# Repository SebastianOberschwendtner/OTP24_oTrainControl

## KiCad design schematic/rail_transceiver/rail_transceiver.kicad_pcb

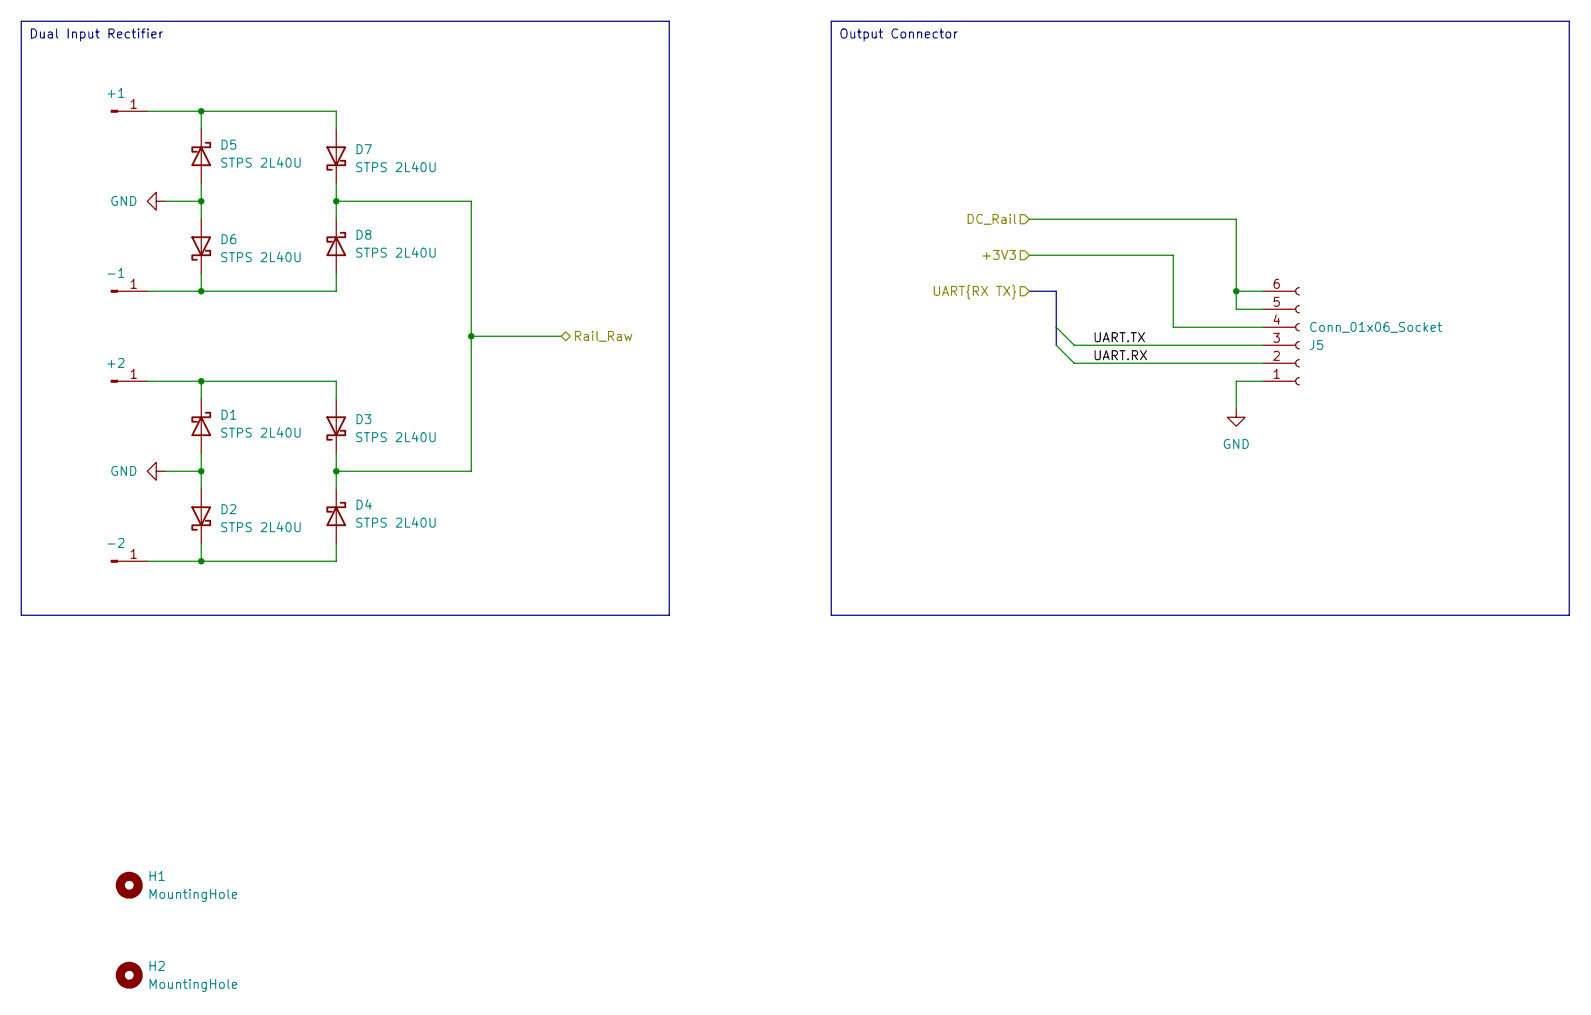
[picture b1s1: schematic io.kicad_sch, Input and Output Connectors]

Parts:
+1, +2: Conn_01x01_Pin; SolderWirePad_1x01_SMD_1x2mm
-1, -2: Conn_01x01_Pin; SolderWirePad_1x01_SMD_1x2mm
D1, D2, D3, D4, D5, D6, D7, D8: STPS 2L40U; D_SMB
H1, H2: MountingHole; MountingHole_2.2mm_M2
J5: Conn_01x06_Socket; Molex_SPOX_5268-06A_1x06_P2.50mm_Horizontal

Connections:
+3V3: J5.4; also elsewhere on the board
/Connectors/DC_Rail: J5.5, J5.6; also elsewhere on the board
/Connectors/Rail_Raw: D3.1 (K), D4.1 (K), D7.1 (K), D8.1 (K); also elsewhere on the board
/Connectors/UART.RX: J5.2; also elsewhere on the board
/Connectors/UART.TX: J5.3; also elsewhere on the board
GND: D1.2 (A), D2.2 (A), D5.2 (A), D6.2 (A), J5.1; also elsewhere on the board
unnamed: +1.1, D5.1 (K), D7.2 (A)
unnamed: +2.1, D1.1 (K), D3.2 (A)
unnamed: -1.1, D6.1 (K), D8.2 (A)
unnamed: -2.1, D2.1 (K), D4.2 (A)

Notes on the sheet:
Output Connector
Dual Input Rectifier

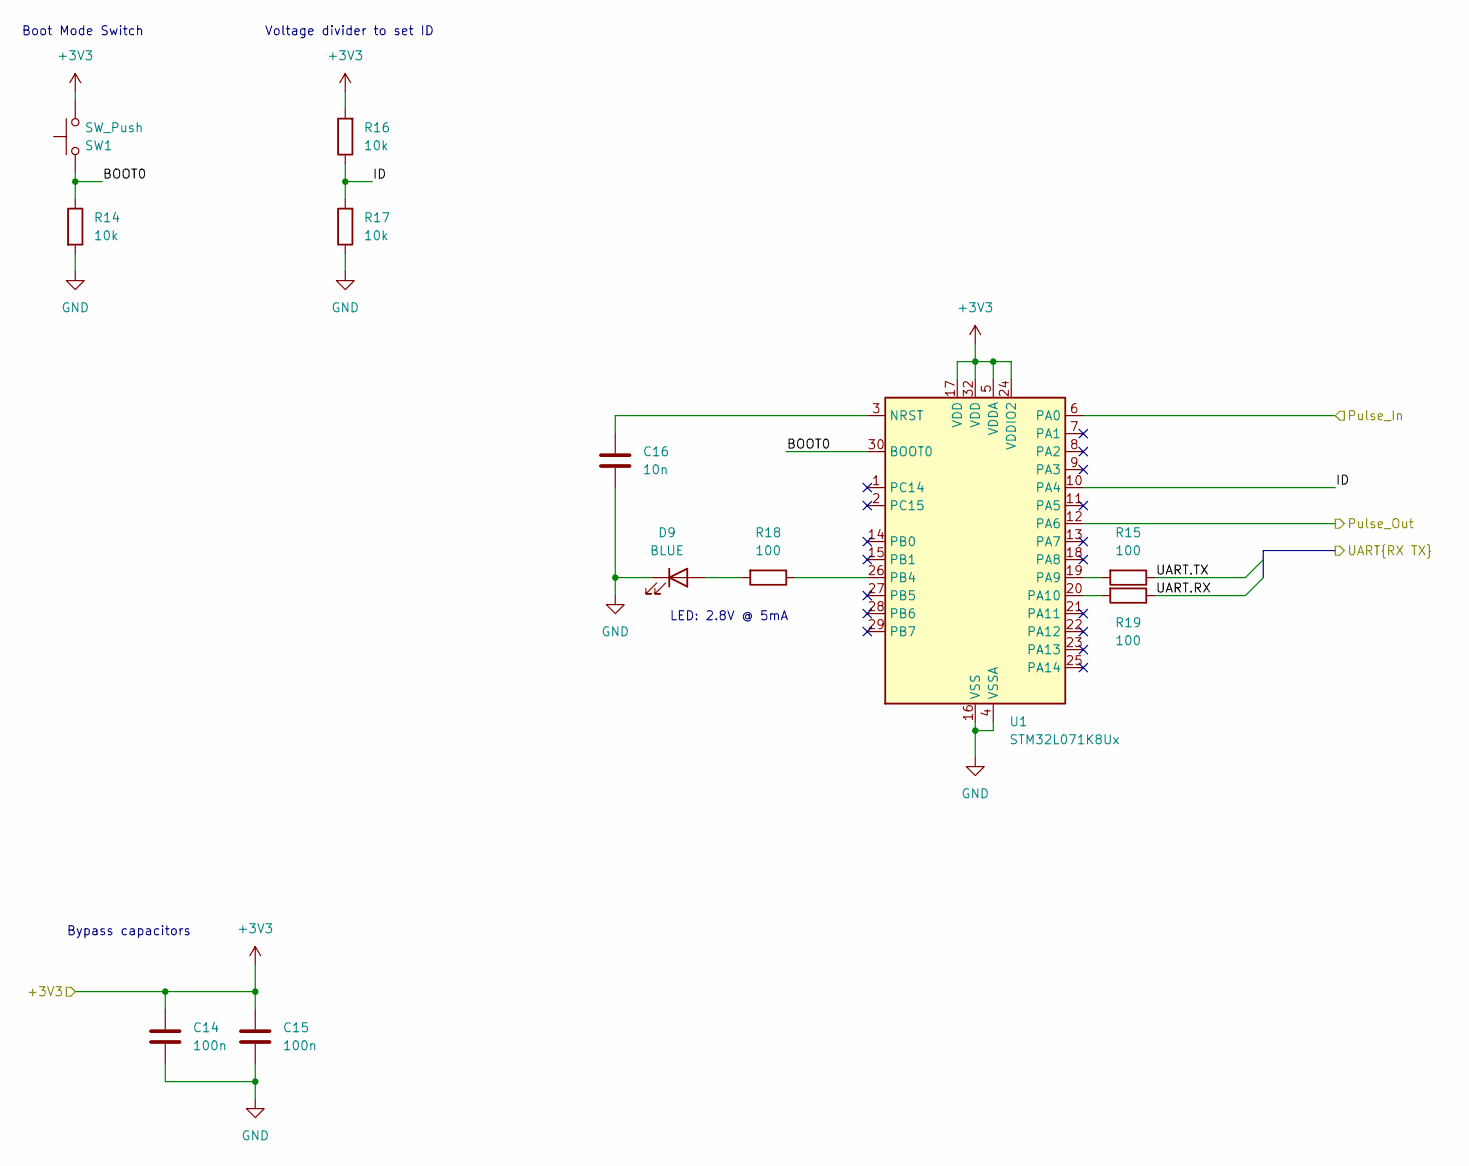
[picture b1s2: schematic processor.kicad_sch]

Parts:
C14, C15: 100n; C_0805_2012Metric_Pad1.18x1.45mm_HandSolder
C16: 10n; C_0805_2012Metric_Pad1.18x1.45mm_HandSolder
D9: BLUE; LED_0603_1608Metric_Pad1.05x0.95mm_HandSolder
R14, R16, R17: 10k; R_0805_2012Metric_Pad1.20x1.40mm_HandSolder
R15, R18, R19: 100; R_0805_2012Metric_Pad1.20x1.40mm_HandSolder
SW1: SW_Push; SW_SPST_Wuerth_WS-TASU_SMT
U1: STM32L071K8Ux; QFN-32-1EP_5x5mm_P0.5mm_EP3.45x3.45mm

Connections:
+3V3: C14.1, C15.1, R16.2, SW1.1, U1.5 (VDDA), U1.17 (VDD), U1.24 (VDDIO2), U1.32 (VDD); also elsewhere on the board
/Connectors/UART.RX: R19.1; also elsewhere on the board
/Connectors/UART.TX: R15.1; also elsewhere on the board
/Front End/Pulse_In: U1.6 (PA0); also elsewhere on the board
/Front End/Pulse_Out: U1.12 (PA6); also elsewhere on the board
/Processor/BOOT0: R14.1, SW1.2, U1.30 (BOOT0)
/Processor/ID: R16.1, R17.2, U1.10 (PA4)
GND: C14.2, C15.2, C16.2, D9.1 (K), R14.2, R17.1, U1.4 (VSSA), U1.16 (VSS), U1.31 (VSS), U1.33 (VSS); also elsewhere on the board
unnamed: D9.2 (A), R18.2
unnamed: C16.1, U1.3 (NRST)
unnamed: R15.2, U1.19 (PA9)
unnamed: R19.2, U1.20 (PA10)
unnamed: R18.1, U1.26 (PB4)

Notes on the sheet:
Bypass capacitors
Voltage divider to set ID
Boot Mode Switch
LED: 2.8V @ 5mA

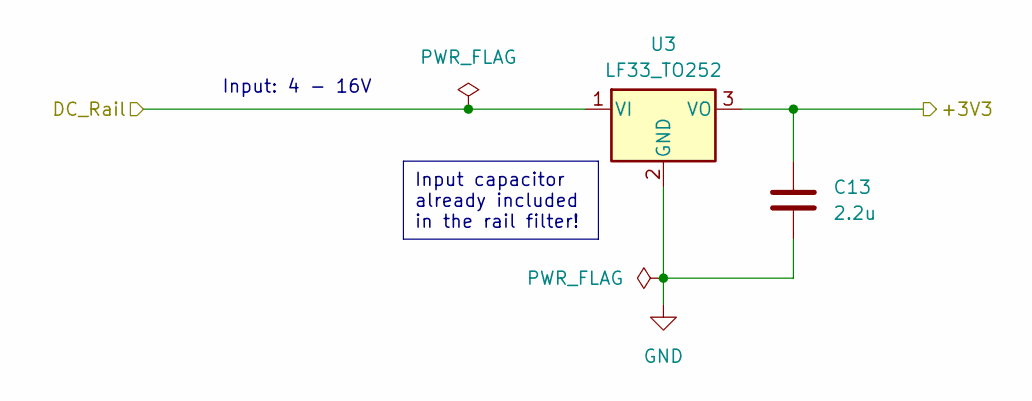
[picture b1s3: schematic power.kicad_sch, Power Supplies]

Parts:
C13: 2.2u; C_0805_2012Metric_Pad1.18x1.45mm_HandSolder
U3: LF33_TO252; TO-252-2

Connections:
+3V3: C13.1, U3.3 (VO); also elsewhere on the board
/Connectors/DC_Rail: U3.1 (VI); also elsewhere on the board
GND: C13.2, U3.2 (GND); also elsewhere on the board

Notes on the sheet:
Input capacitor already included in the rail filter!
Input: 4 - 16V

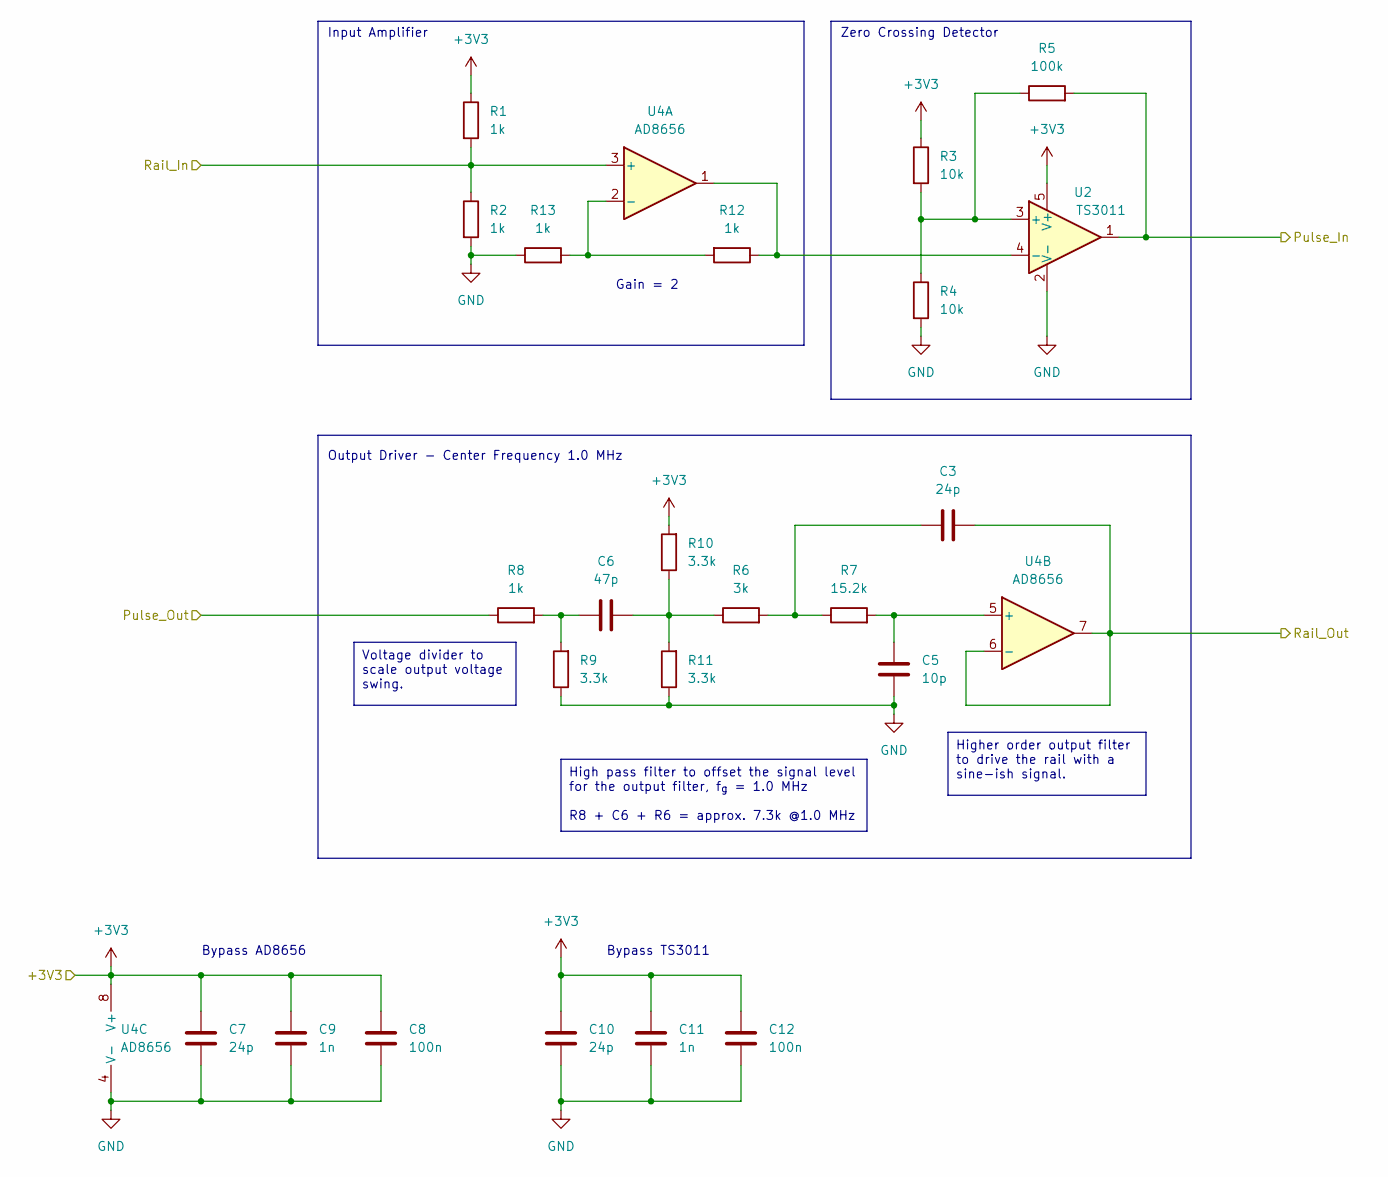
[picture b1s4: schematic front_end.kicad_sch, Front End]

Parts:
C3, C7, C10: 24p; C_0805_2012Metric_Pad1.18x1.45mm_HandSolder
C5: 10p; C_0805_2012Metric_Pad1.18x1.45mm_HandSolder
C6: 47p; C_0805_2012Metric_Pad1.18x1.45mm_HandSolder
C8, C12: 100n; C_0805_2012Metric_Pad1.18x1.45mm_HandSolder
C9, C11: 1n; C_0805_2012Metric_Pad1.18x1.45mm_HandSolder
R1, R2, R8, R12, R13: 1k; R_0805_2012Metric_Pad1.20x1.40mm_HandSolder
R3, R4: 10k; R_0805_2012Metric_Pad1.20x1.40mm_HandSolder
R5: 100k; R_0805_2012Metric_Pad1.20x1.40mm_HandSolder
R6: 3k; R_0805_2012Metric_Pad1.20x1.40mm_HandSolder
R7: 15.2k; R_0805_2012Metric_Pad1.20x1.40mm_HandSolder
R9, R10, R11: 3.3k; R_0805_2012Metric_Pad1.20x1.40mm_HandSolder
U2: TS3011; SOT-23-5_HandSoldering
U4: AD8656; MSOP-8_3x3mm_P0.65mm

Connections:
+3V3: C7.2, C8.2, C9.2, C10.2, C11.2, C12.2, R1.1, R3.1, R10.2, U2.5 (V+), U4.8 (V+); also elsewhere on the board
/Front End/Pulse_In: R5.2, U2.1; also elsewhere on the board
/Front End/Pulse_Out: R8.1; also elsewhere on the board
/Front End/Rail_In: R1.2, R2.1, U4.3 (+); also elsewhere on the board
/Front End/Rail_Out: C3.2, U4.6 (-), U4.7; also elsewhere on the board
GND: C5.1, C7.1, C8.1, C9.1, C10.1, C11.1, C12.1, R2.2, R4.2, R9.1, R11.1, R13.1, U2.2 (V-), U4.4 (V-); also elsewhere on the board
unnamed: C3.1, R6.2, R7.1
unnamed: C6.1, R6.1, R10.1, R11.2
unnamed: C6.2, R8.2, R9.2
unnamed: R3.2, R4.1, R5.1, U2.3 (+)
unnamed: R12.1, U2.4 (-), U4.1
unnamed: R12.2, R13.2, U4.2 (-)
unnamed: C5.2, R7.2, U4.5 (+)

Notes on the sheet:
High pass filter to offset the signal level for the output filter, f_{g} = 1.0 MHz R8 + C6 + R6 = approx. 7.3k @1.0 MHz
Voltage divider to scale output voltage swing.
Higher order output filter to drive the rail with a sine-ish signal.
Gain = 2
Output Driver - Center Frequency 1.0 MHz
Bypass AD8656
Bypass TS3011
Input Amplifier
Zero Crossing Detector

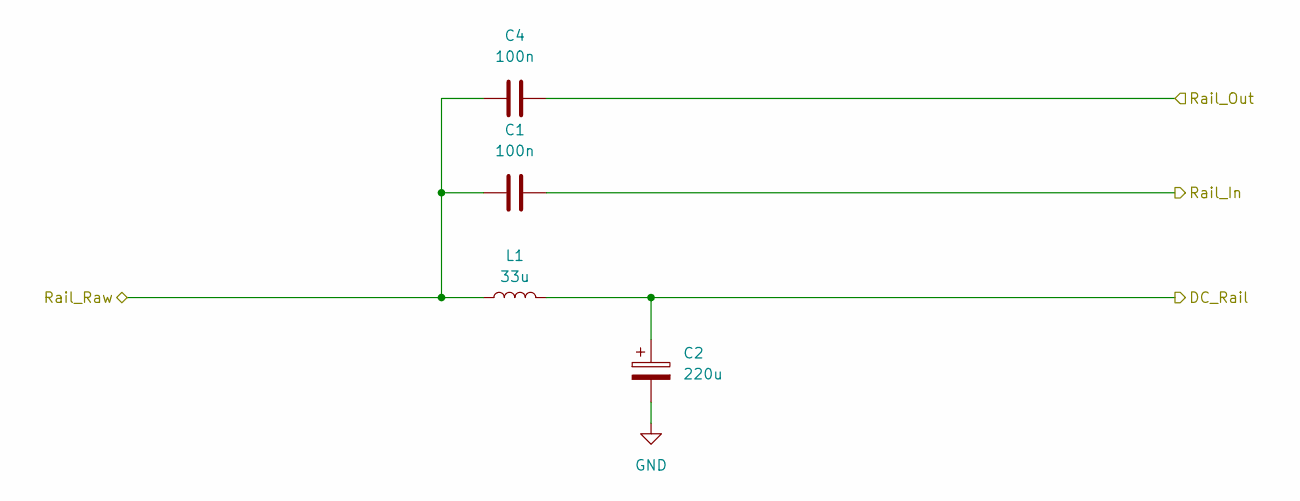
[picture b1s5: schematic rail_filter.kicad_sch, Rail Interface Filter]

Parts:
C1, C4: 100n; C_0805_2012Metric_Pad1.18x1.45mm_HandSolder
C2: 220u; CP_Elec_6.3x7.7
L1: 33u; L_Bourns_SRN5040

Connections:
/Connectors/DC_Rail: C2.1, L1.2; also elsewhere on the board
/Connectors/Rail_Raw: C1.2, C4.2, L1.1; also elsewhere on the board
/Front End/Rail_In: C1.1; also elsewhere on the board
/Front End/Rail_Out: C4.1; also elsewhere on the board
GND: C2.2; also elsewhere on the board

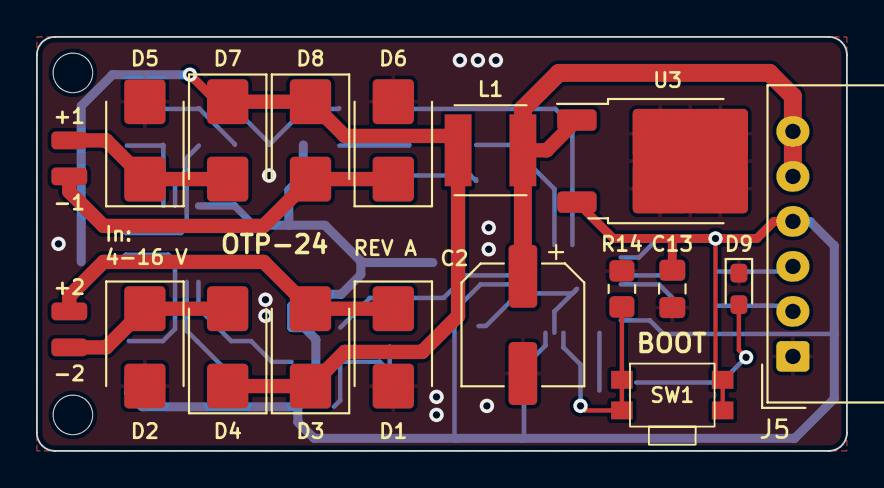
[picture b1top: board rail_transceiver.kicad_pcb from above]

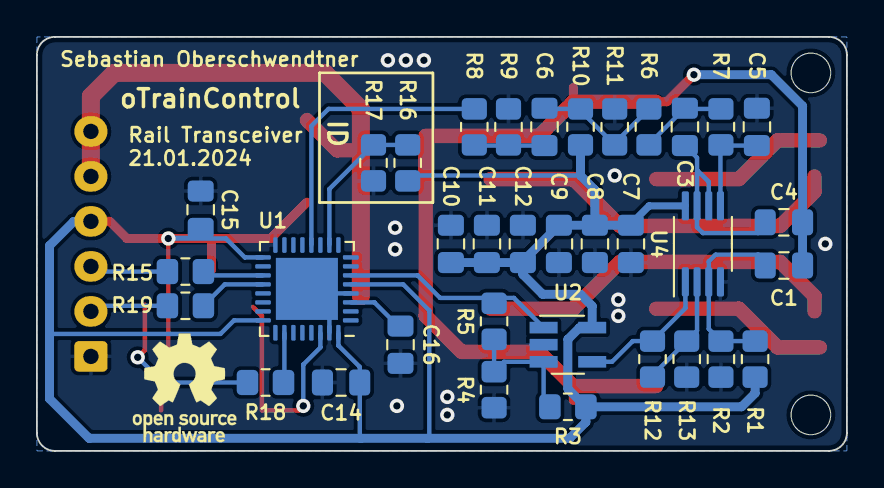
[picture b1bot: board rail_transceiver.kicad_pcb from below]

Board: 2 copper layers, 45.0 x 23.0 mm, 57 parts (35 on the bottom side), 28 nets.

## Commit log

2023-12-08 Initial commit of project.
2023-12-08 Create LICENSE
2023-12-08 Completes folder structure.
2023-12-09 Adds further developer files.
2023-12-10 :art: Adds first version of loop analysis.
2023-12-23 :tada: Simulation can design and analyze the loop.
2024-01-04 Removes simulation as it is no longer part of the project.
2024-01-21 :nut_and_bolt: Initial PCB of rail transceiver.
2024-04-25 Removes Pipfiles which are left over from simulation.
2024-04-25 🛠️ Adds reference to OTOS submodule.
